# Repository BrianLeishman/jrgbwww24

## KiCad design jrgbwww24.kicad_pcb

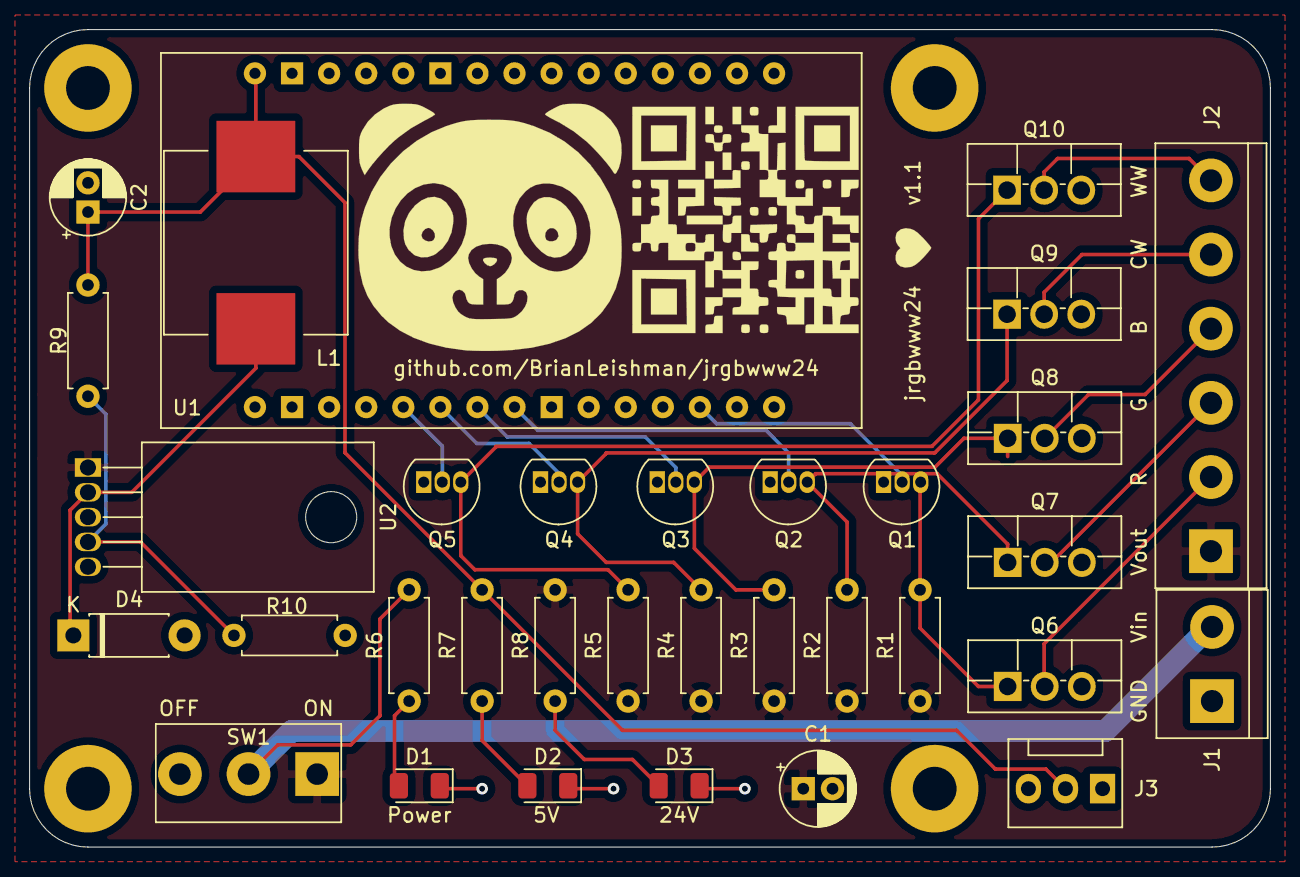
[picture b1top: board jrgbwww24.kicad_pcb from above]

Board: 2 copper layers, 85.0 x 56.0 mm, 33 parts (0 on the bottom side), 24 nets.

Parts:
C1: 100u; CP_Radial_D5.0mm_P2.00mm
C2: 330u; CP_Radial_D5.0mm_P2.00mm
D1: RED - ALWAYS ON; LED_1206_3216Metric
D2: GREEN - 5V; LED_1206_3216Metric
D3: BLUE - 24V; LED_1206_3216Metric
D4: SB160-E3/73; D_DO-41_SOD81_P7.62mm_Horizontal
J1: Srew_terminal; TerminalBlock_bornier-2_P5.08mm
J2: Screw_Terminal_01x06; TerminalBlock_bornier-6_P5.08mm
J3: Fan; FanPinHeader_1x03_P2.54mm_Vertical
L1: 330u; L_Wuerth_WE-PD-Typ-LS_Handsoldering
Q1, Q2, Q3, Q4, Q5: 2N3904; TO-92_Inline
Q6, Q7, Q8, Q9, Q10: IPA040N06N; TO-220F-3_Vertical
R1, R2, R3, R4, R5: 10K; R_Axial_DIN0207_L6.3mm_D2.5mm_P7.62mm_Horizontal
R6: 1.1K; R_Axial_DIN0207_L6.3mm_D2.5mm_P7.62mm_Horizontal
R7: 100; R_Axial_DIN0207_L6.3mm_D2.5mm_P7.62mm_Horizontal
R8: 1.05K; R_Axial_DIN0207_L6.3mm_D2.5mm_P7.62mm_Horizontal
R9: 6.12k; R_Axial_DIN0207_L6.3mm_D2.5mm_P7.62mm_Horizontal
R10: 2k; R_Axial_DIN0207_L6.3mm_D2.5mm_P7.62mm_Horizontal
SW1: SW_SPDT; 1P2T SPDT
U1: esp8266; KeeYees ESP8266 ESP-12E
U2: TL2575; TO-220-5_Horizontal_TabDown

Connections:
+5V: C2.1, J3.2, L1.2, R7.2, R9.1, U1.15
+24V: C1.1, J2.1, R1.1, R2.1, R3.1, R4.1, R5.1, R8.2, SW1.1, U2.1
/B_GND: J2.4, Q8.2
/B_SIGNAL: Q3.2, U1.24
/CW_GND: J2.5, Q9.2
/CW_SIGNAL: Q4.2, U1.25
/G_GND: J2.3, Q7.2
/G_SIGNAL: Q2.2, U1.23
/R_GND: J2.2, Q6.2
/R_SIGNAL: Q1.2, U1.18
/WW_GND: J2.6, Q10.2
/WW_SIGNAL: Q5.2, U1.26
Earth: C1.2, C2.2, D1.1, D2.1, D3.1, D4.2, J1.1, J3.1, Q1.1, Q2.1, Q3.1, Q4.1, Q5.1, Q6.3, Q7.3, Q8.3, Q9.3, Q10.3, R10.2, U1.10, U1.14, U1.22, U1.29, U2.3, U2.5
unnamed: D1.2, R6.1
unnamed: D2.2, R7.1
unnamed: D3.2, R8.1
unnamed: D4.1, L1.1, U2.2
unnamed: Q1.3, Q6.1, R1.2
unnamed: Q2.3, Q7.1, R2.2
unnamed: Q3.3, Q8.1, R3.2
unnamed: Q4.3, Q9.1, R4.2
unnamed: Q5.3, Q10.1, R5.2
unnamed: R9.2, R10.1, U2.4
VDD: J1.2, R6.2, SW1.2

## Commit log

2021-09-21 labeled connections
2021-09-23 schmea refactor
2021-09-23 annotations
2021-09-23 fixed all erc errors, updated esp symbol
2021-09-28 some footprints
2021-10-07 traces!
2021-10-07 gerber file
2021-10-07 gerber files and drill files
2021-10-07 screenshots
2021-10-07 3d screenshot
2021-10-16 fixed footprints, schematics
2021-10-16 improved 5v, fan header
2021-10-16 gerber files, updated renders
2021-10-16 readme
2022-01-07 fixed 5 v power supply
2022-01-07 updated renders
